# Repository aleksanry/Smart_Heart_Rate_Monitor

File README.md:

# Smart Heart Rate Monitor 💓

A comprehensive Arduino-based heart rate monitoring system featuring real-time BPM detection, customizable alarms, and an intuitive OLED interface.

## ✨ Features

- **📊 Real-time Heart Rate Monitoring** - Continuous BPM detection with rolling average
- **🖥️ OLED Display Interface** - Clear, intuitive menu system
- **🚨 Smart Alarm System** - Customizable high/low BPM thresholds
- **📈 Session Statistics** - Track min/max BPM and session duration
- **💡 Visual Indicators** - LED status feedback and heartbeat animation
- **⚙️ User-Friendly Controls** - Three-button navigation system
- **🔧 Sensor Calibration** - Built-in sensor status monitoring

## 🛠️ Hardware Requirements

### Components
- **Arduino Nano v3.x** - Main microcontroller
- **MAX30102** - Heart rate and pulse oximetry sensor
- **SSD1306 OLED Display** (128x64) - User interface
- **3x Push Buttons** (SW1, SW2, SW3) - User input
- **1x LED** (D1) - Status indicator
- **3x Pull-up Resistors** (1kΩ) - Button debouncing
- **3x Capacitors** (100nF) - Power filtering

### Pin Connections

| Component | Arduino Pin | Notes |
|-----------|-------------|-------|
| MAX30102 SDA | A4 | I2C Data |
| MAX30102 SCL | A5 | I2C Clock |
| OLED SDA | A4 | I2C Data |
| OLED SCL | A5 | I2C Clock |
| SW1 (Menu) |pin D2 | Analog input with pull-up |
| SW2 (Up) | pin D3 | Analog input with pull-up |
| SW3 (Down) | pin D4 | Analog input with pull-up |
| Status LED | Pin D12 | Digital output |
| Power | 5V/3.3V | VCC connection |
| Ground | GND | Common ground |

## 📚 Software Requirements

### Arduino Libraries
Install these libraries through the Arduino Library Manager:

```
Adafruit SSD1306        // OLED display driver
Adafruit GFX Library    // Graphics library
MAX30105lib             // SparkFun MAX3010x sensor library
```

### Library Installation
1. Open Arduino IDE
2. Go to **Sketch → Include Library → Manage Libraries**
3. Search and install each library listed above
4. Restart Arduino IDE

## 🚀 Installation & Setup

### 1. Hardware Assembly
- Follow the pin connection table above
- Ensure proper power connections (3.3V or 5V)
- Connect I2C devices to the same bus (SDA/SCL)
- Add pull-up resistors to button connections
### 2. Software Upload
```bash
# Clone the repository
git clone https://github.com/Aleksanry/Smart_Heart_Rate_Monitor.git

# Open the Arduino file
# HR_Monitor_Firmware/HR_Monitor_Firmware.ino

# Select your board: Arduino Nano
# Select the correct COM port
# Click Upload
```
### 3. Sensor Calibration
1. Power on the device
2. Navigate to **Settings Menu → Sensor Config**
3. Ensure IR signal shows values > 10000 when finger is placed
4. If values are low, check sensor connections

## 🎮 User Interface Guide

### Button Controls
- **SW1 (Menu)** - Navigate between screens, confirm selections
- **SW2 (Up)** - Navigate up, increase values
- **SW3 (Down)** - Navigate down, decrease values

### Screen Navigation
```
Main Screen
    ↓ (SW1)
Settings Menu
    ↓ (SW1)
┌─ Alarm Settings
└─ Sensor Calibration
```

### Main Display Elements
- **Large BPM Reading** - Current heart rate
- **Status Indicator** - LOW/NORMAL/HIGH
- **Alarm Status** - ON/OFF indication
- **Session Timer** - Minutes and seconds elapsed
- **Heartbeat Animation** - Visual pulse indicator
- **Alarm Banner** - Flashing when triggered

## ⚙️ Configuration Options

### Alarm Settings
- **Minimum BPM**: Default 60, Range 30-120
- **Maximum BPM**: Default 100, Range 80-220
- **Alarm Enable/Disable**: Toggle alarm functionality

### Sensor Parameters
- **LED Brightness**: 60 (adjustable in code)
- **Sample Rate**: 400 Hz
- **Sample Average**: 4 readings
- **Pulse Width**: 411 µs

## 🔍 Troubleshooting

### Common Issues

**No Heart Rate Reading**
- Check sensor placement (fingertip on sensor)
- Verify MAX30102 connections
- Ensure adequate lighting conditions
- Check I2C address (default 0x57)

**Display Not Working**
- Verify OLED connections (SDA/SCL)
- Check I2C address (default 0x3C)
- Ensure adequate power supply

**Buttons Not Responding**
- Check analog pin connections
- Verify pull-up resistors are installed
- Test button continuity

**Inaccurate Readings**
- Keep finger steady during measurement
- Avoid excessive pressure on sensor
- Wait for stabilization (10-15 seconds)

### Debug Mode
Enable serial monitoring at 115200 baud for diagnostic information:
```cpp
Serial.begin(115200);  // Already included in code
```

## 📊 Technical Specifications

### Performance
- **Update Rate**: 20ms sensor reading, 500ms display refresh
- **Accuracy**: ±2 BPM (typical)
- **Range**: 20-220 BPM
- **Response Time**: 3-5 seconds for stable reading

### Power Consumption
- **Active Mode**: ~50mA @ 5V
- **Display On**: ~30mA additional
- **Sensor Active**: ~15mA additional

### Memory Usage
- **Program Memory**: ~75% of Arduino Nano
- **Dynamic Memory**: ~60% of available RAM

## 🔧 Customization

### Modifying Thresholds
```cpp
// Default alarm thresholds (in setup())
int minHeartRate = 60;    // Lower limit
int maxHeartRate = 100;   // Upper limit
```

### Display Update Rate
```cpp
// Update intervals (in milliseconds)
const unsigned long DISPLAY_UPDATE_INTERVAL = 500;  // 500ms
const unsigned long SENSOR_READ_INTERVAL = 20;      // 20ms
```

### LED Behavior
```cpp
// Alarm LED patterns
digitalWrite(LED_PIN, (millis() / 250) % 2);  // Fast blink (250ms)
digitalWrite(LED_PIN, (millis() / 1000) % 2); // Slow blink (1000ms)
```

### Code Style Guidelines
- Use descriptive variable names
- Comment complex algorithms
- Follow Arduino naming conventions
- Test on actual hardware before submitting

## 🙏 Acknowledgments

- **SparkFun** for the excellent MAX30105 library
- **Adafruit** for the comprehensive display libraries
- **Arduino Community** for continuous support and inspiration

## 🔮 Future Enhancements

- [ ] Bluetooth connectivity for data logging
- [ ] SD card storage for long-term monitoring
- [ ] Mobile app integration
- [ ] Multiple user profiles
- [ ] Advanced analytics and trends
- [ ] Voice alerts
- [ ] Battery level monitoring

---

**⚠️ Medical Disclaimer**: This device is for educational and recreational purposes only. It is not intended for medical diagnosis or treatment. Always consult healthcare professionals for medical advice.

---

Made with ❤️ by Nermin | Arduino Heart Rate Monitor v1.0

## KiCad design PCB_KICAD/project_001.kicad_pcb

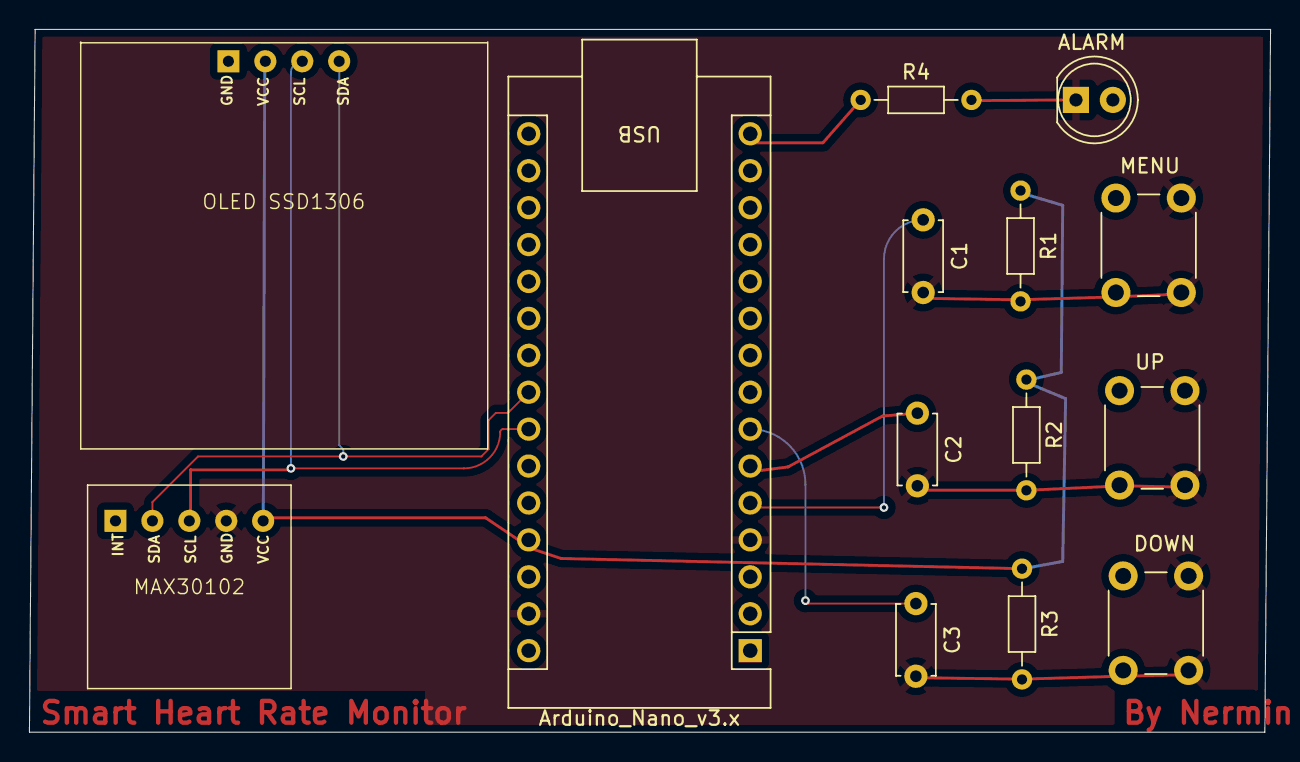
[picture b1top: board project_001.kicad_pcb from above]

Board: 4 copper layers, 85.4 x 48.3 mm, 14 parts (0 on the bottom side), 10 nets.

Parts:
ALARM: LED; LED_D5.0mm
Arduino_Nano_v3.x: Arduino_Nano_v3.x; Arduino_Nano
C1, C2, C3: 100n; C_Disc_D4.7mm_W2.5mm_P5.00mm
DOWN: SW_Push; SW_PUSH_6mm
MAX30102: MAX30102
MENU: SW_Push; SW_PUSH_6mm
OLED SSD1306: SSD1306
R1, R2, R3, R4: 1k; R_Axial_DIN0204_L3.6mm_D1.6mm_P7.62mm_Horizontal
UP: SW_Push; SW_PUSH_6mm

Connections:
+5V: Arduino_Nano_v3.x.27 (+5V), R1.1, R2.1, R3.1
GND: ALARM.1 (K), Arduino_Nano_v3.x.4 (GND), Arduino_Nano_v3.x.29 (GND), C1.2, C2.2, C3.2, DOWN.1, MAX30102.4 (GND), MENU.1, UP.1
unnamed: Arduino_Nano_v3.x.23 (A4), MAX30102.2 (SDA), OLED SSD1306.4 (SDL)
unnamed: Arduino_Nano_v3.x.24 (A5), MAX30102.3 (SCL), OLED SSD1306.3 (SCL)
unnamed: Arduino_Nano_v3.x.5 (D2), C1.1, MENU.2, R1.2
unnamed: Arduino_Nano_v3.x.6 (D3), C2.1, R2.2, UP.2
unnamed: Arduino_Nano_v3.x.7 (D4), C3.1, DOWN.2, R3.2
unnamed: Arduino_Nano_v3.x.15 (D12), R4.1
unnamed: ALARM.2 (A), R4.2
VCC: MAX30102.5 (VCC), OLED SSD1306.2 (VCC)
